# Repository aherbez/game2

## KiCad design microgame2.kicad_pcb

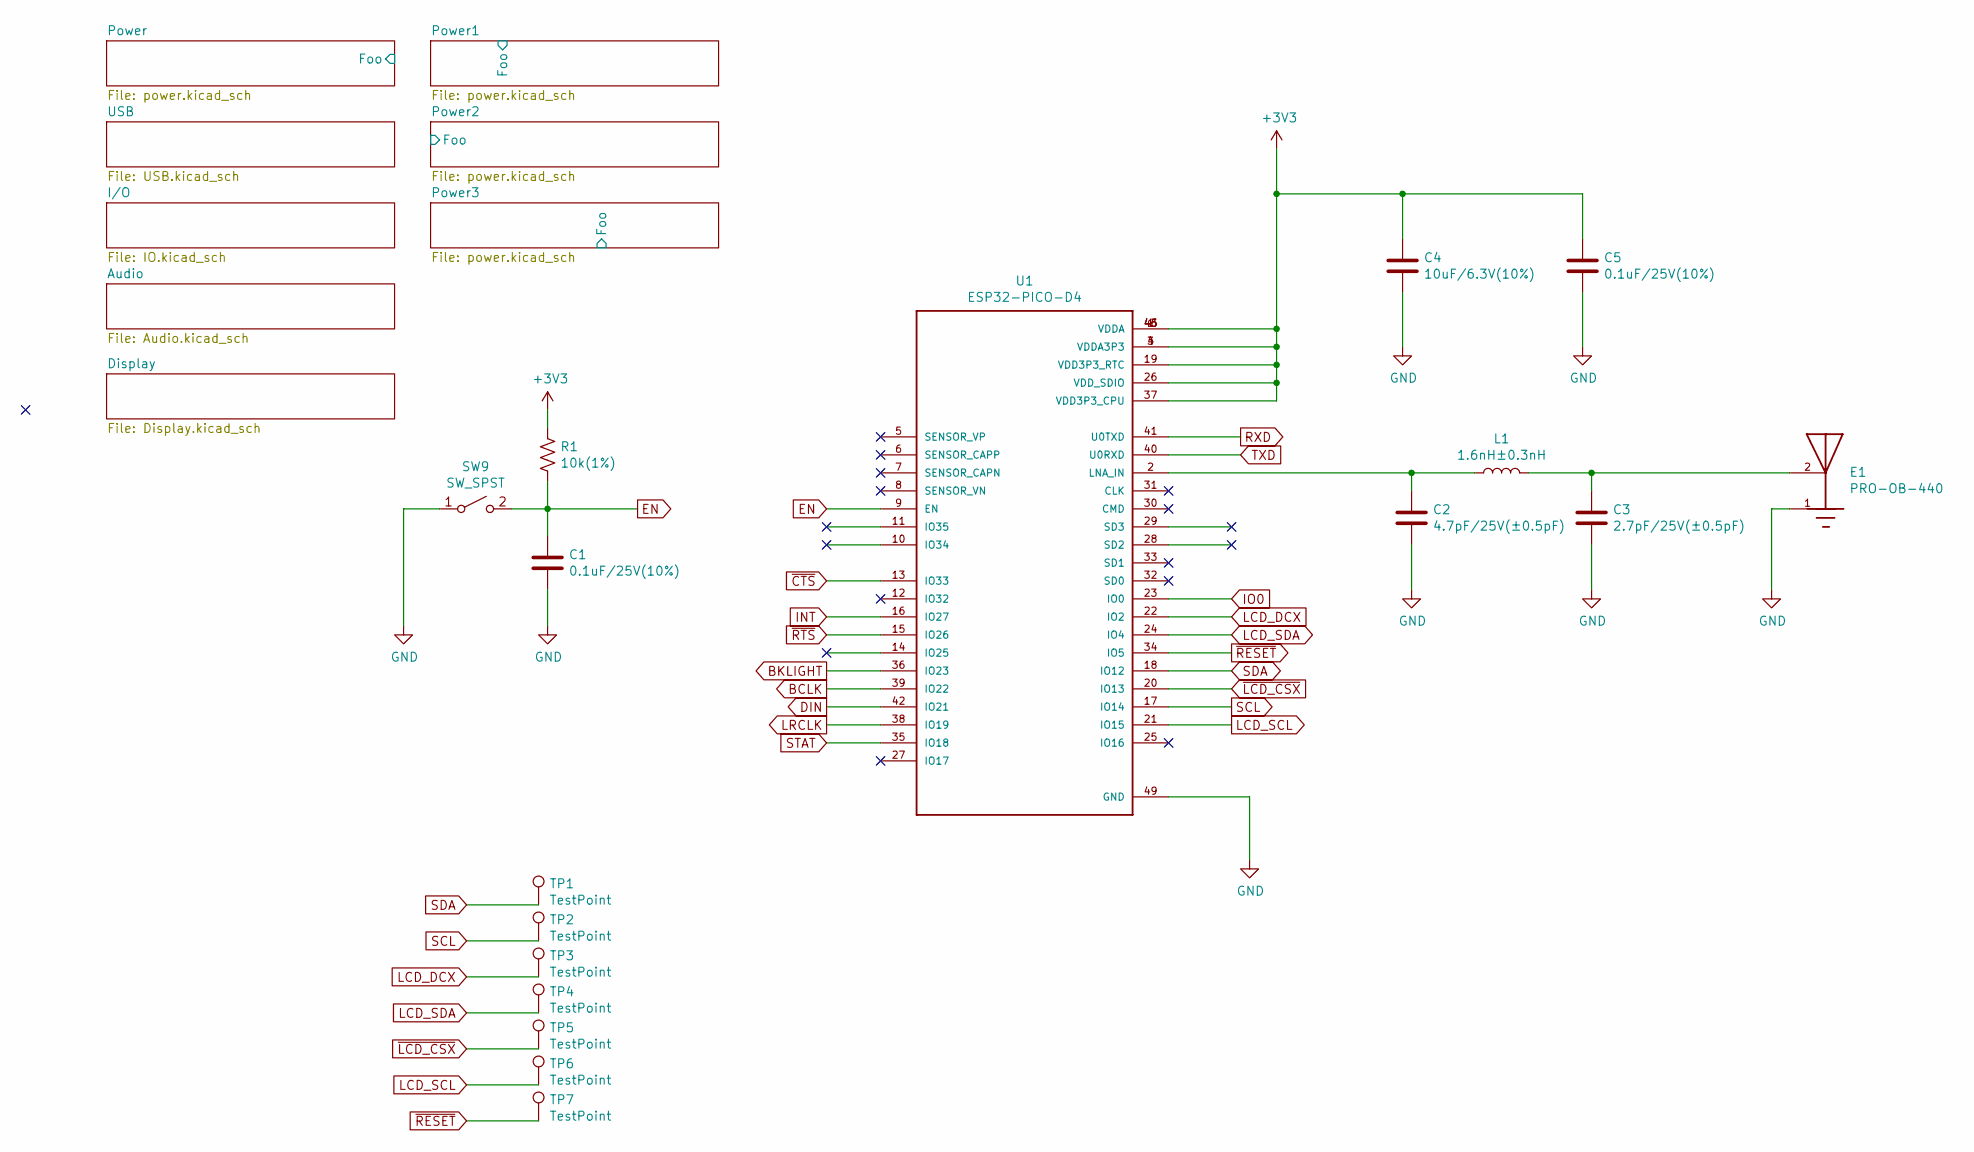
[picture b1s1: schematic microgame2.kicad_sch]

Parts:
C1, C5: 0.1uF/25V(10%); C_0402_1005Metric
C2: 4.7pF/25V(±0.5pF); C_0402_1005Metric
C3: 2.7pF/25V(±0.5pF); C_0402_1005Metric
C4: 10uF/6.3V(10%); C_0603_1608Metric
E1: PRO-OB-440; ANT_PRO-OB-440
L1: 1.6nH±0.3nH; C_0402_1005Metric
R1: 10k(1%); C_0402_1005Metric
SW9: SW_SPST; EVPAE
TP1, TP2, TP3, TP4, TP5, TP6, TP7: TestPoint; TestPoint_Pad_D1.0mm
U1: ESP32-PICO-D4; PQFN50P700X700X104-49N

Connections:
+3V3: C4.1, C5.1, R1.1, U1.1 (VDDA), U1.3 (VDDA3P3), U1.4 (VDDA3P3), U1.19 (VDD3P3_RTC), U1.26 (VDD_SDIO), U1.37 (VDD3P3_CPU), U1.43 (VDDA), U1.46 (VDDA); also elsewhere on the board
BCLK: U1.39 (IO22); also elsewhere on the board
BKLIGHT: U1.36 (IO23); also elsewhere on the board
DIN: U1.42 (IO21); also elsewhere on the board
EN: C1.1, R1.2, SW9.2 (B), U1.9 (EN); also elsewhere on the board
GND: C1.2, C2.2, C3.2, C4.2, C5.2, E1.1, SW9.1 (A), U1.49 (GND); also elsewhere on the board
INT: U1.16 (IO27); also elsewhere on the board
IO0: U1.23 (IO0); also elsewhere on the board
LCD_DCX: TP3.1, U1.22 (IO2); also elsewhere on the board
LCD_SCL: TP6.1, U1.21 (IO15); also elsewhere on the board
LCD_SDA: TP4.1, U1.24 (IO4); also elsewhere on the board
LRCLK: U1.38 (IO19); also elsewhere on the board
unnamed: C2.1, L1.1, U1.2 (LNA_IN)
unnamed: C3.1, E1.2, L1.2
RXD: U1.41 (U0TXD); also elsewhere on the board
SCL: TP2.1, U1.17 (IO14); also elsewhere on the board
SDA: TP1.1, U1.18 (IO12); also elsewhere on the board
STAT: U1.35 (IO18); also elsewhere on the board
TXD: U1.40 (U0RXD); also elsewhere on the board
~CTS: U1.13 (IO33); also elsewhere on the board
~LCD_CSX: TP5.1, U1.20 (IO13); also elsewhere on the board
~RESET: TP7.1, U1.34 (IO5); also elsewhere on the board
~RTS: U1.15 (IO26); also elsewhere on the board

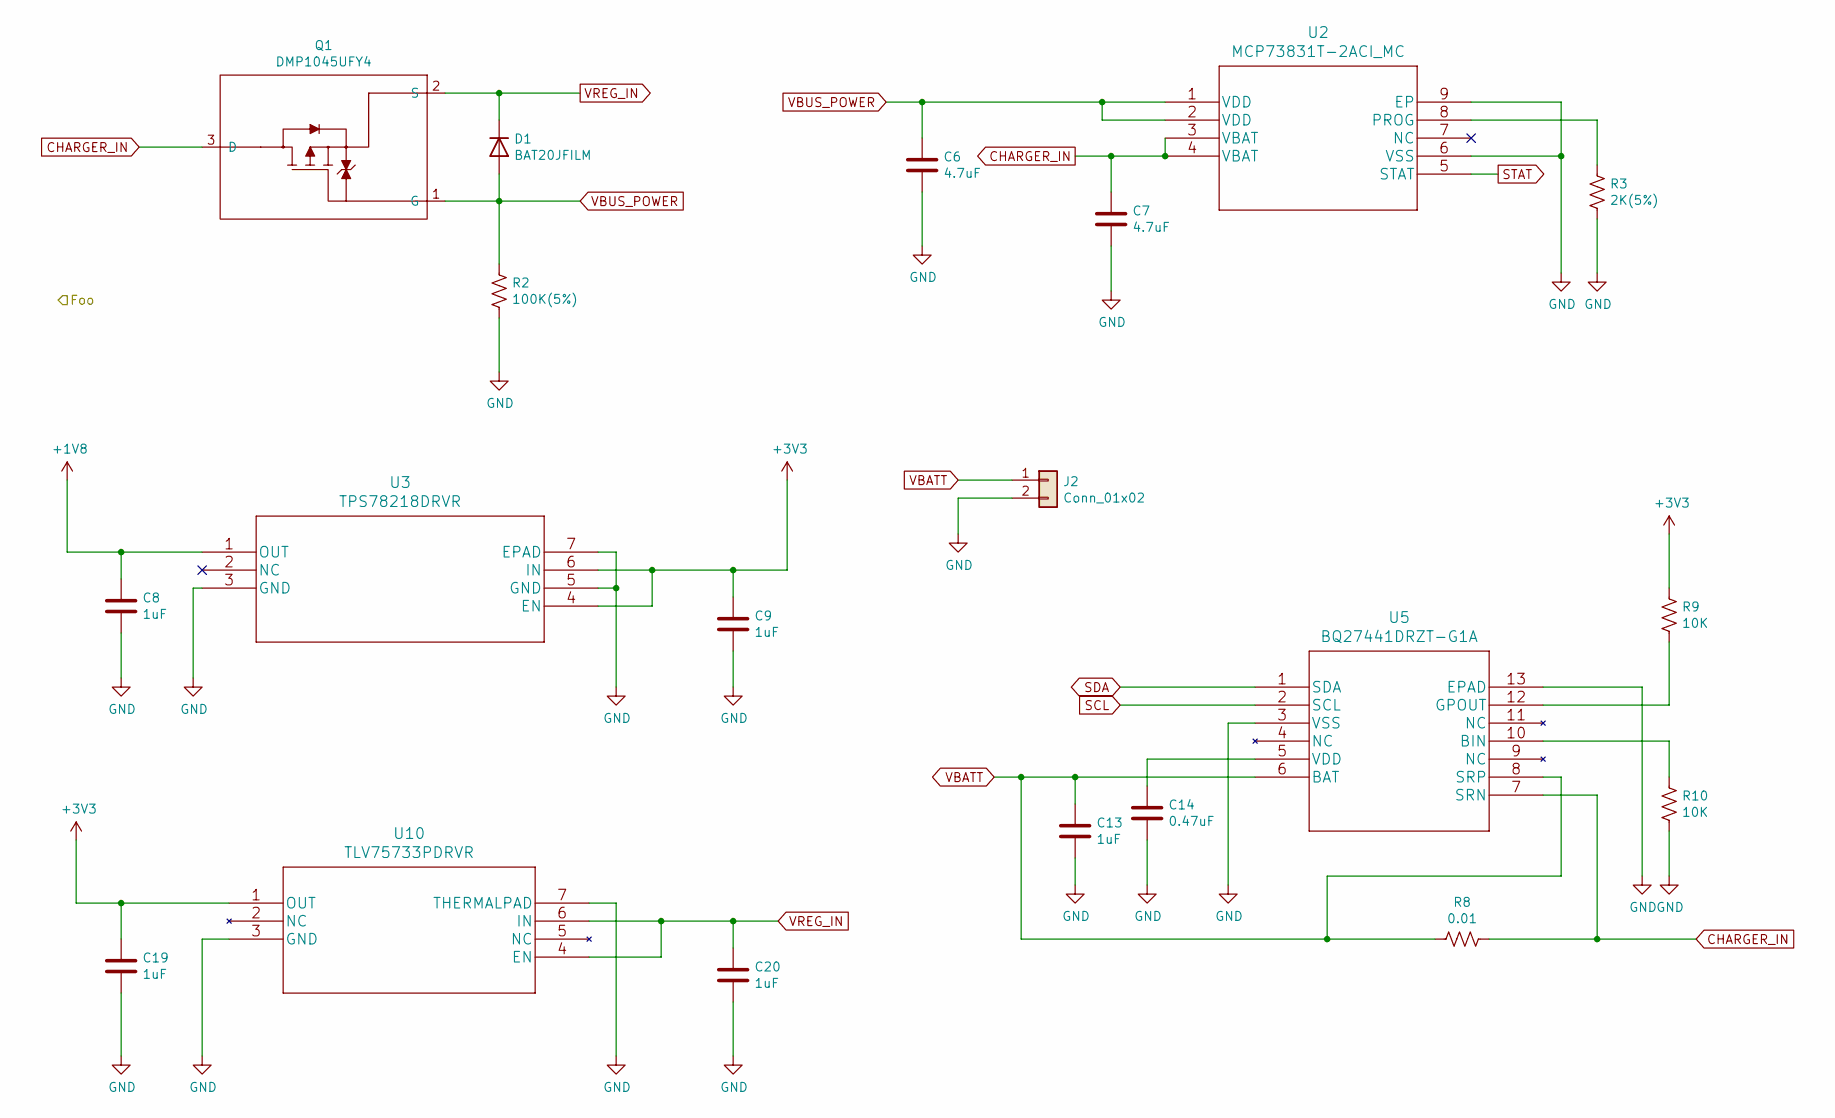
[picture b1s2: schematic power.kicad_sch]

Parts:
C6, C7: 4.7uF; R_0603_1608Metric
C8, C9, C13, C19, C20: 1uF; R_0603_1608Metric
C14: 0.47uF; R_0402_1005Metric
D1: ‎BAT20JFILM; BAT20JFILM
J2: Conn_01x02; R_1206_3216Metric
Q1: DMP1045UFY4; X2-DFN2015-3
R2: 100K(5%); R_0402_1005Metric
R3: 2K(5%); R_0402_1005Metric
R8: 0.01; R_1206_3216Metric
R9, R10: 10K; R_0402_1005Metric
U2: MCP73831T-2ACI_MC; MCP73831T-2ACI&slash_MC
U3: TPS78218DRVR
U5: BQ27441DRZT-G1A
U10: TLV75733PDRVR

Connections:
+1V8: C8.1, U3.1 (OUT); also elsewhere on the board
+3V3: C9.1, C19.1, R9.1, U3.4 (EN), U3.6 (IN), U10.1 (OUT); also elsewhere on the board
CHARGER_IN: C7.1, Q1.3 (D), R8.1, U2.3 (VBAT), U2.4 (VBAT), U5.7 (SRN)
GND: C6.2, C7.2, C8.2, C9.2, C13.2, C14.2, C19.2, C20.2, J2.2, R2.2, R3.2, R10.2, U2.6 (VSS), U2.9 (EP), U3.3 (GND), U3.5 (GND), U3.7 (EPAD), U5.3 (VSS), U5.13 (EPAD), U10.3 (GND), U10.7 (THERMALPAD); also elsewhere on the board
unnamed: C14.1, U5.5 (VDD)
unnamed: R3.1, U2.8 (PROG)
unnamed: R9.2, U5.12 (GPOUT)
unnamed: R10.1, U5.10 (BIN)
SCL: U5.2 (SCL); also elsewhere on the board
SDA: U5.1 (SDA); also elsewhere on the board
STAT: U2.5 (STAT); also elsewhere on the board
VBATT: C13.1, J2.1, R8.2, U5.6 (BAT), U5.8 (SRP)
VBUS_POWER: C6.1, D1.2 (A), Q1.1 (G), R2.1, U2.1 (VDD), U2.2 (VDD); also elsewhere on the board
VREG_IN: C20.1, D1.1 (K), Q1.2 (S), U10.4 (EN), U10.6 (IN)

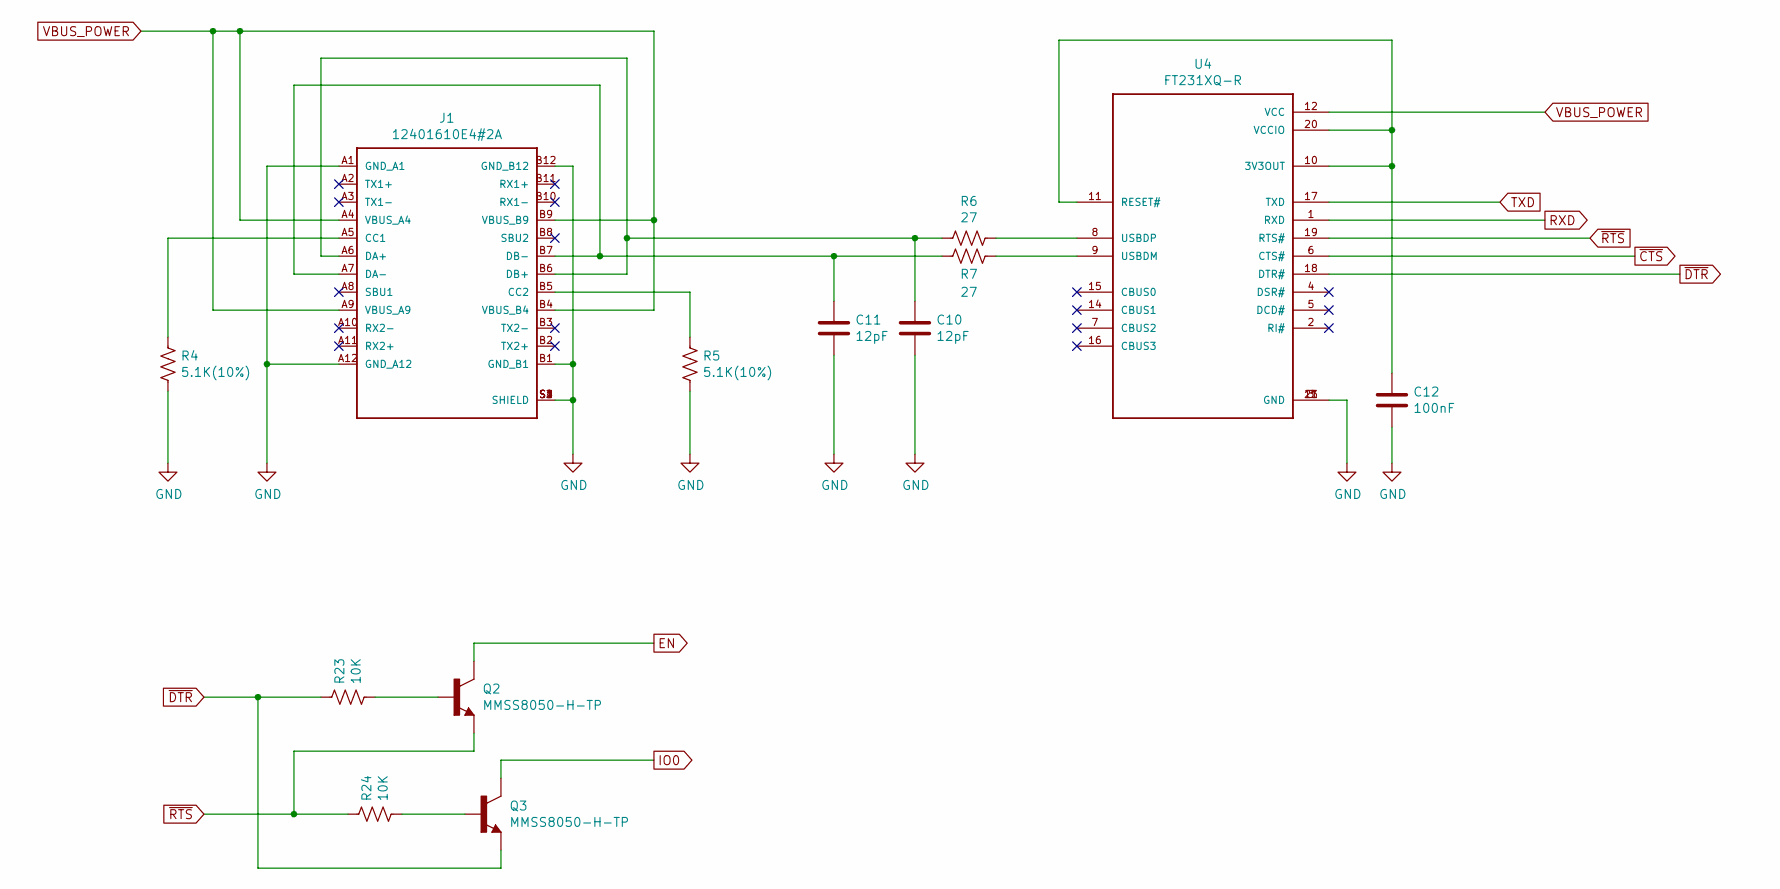
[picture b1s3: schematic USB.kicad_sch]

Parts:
C10, C11: 12pF; R_0402_1005Metric
C12: 100nF; R_0402_1005Metric
J1: 12401610E4#2A; AMPHENOL_12401610E4#2A
Q2, Q3: MMSS8050-H-TP; TRANS_MMSS8050-H-TP
R4, R5: 5.1K(10%); R_0402_1005Metric
R6, R7: 27; R_0402_1005Metric
R23, R24: 10K; R_0402_1005Metric
U4: FT231XQ-R; QFN50P400X400X80-21N

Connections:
EN: Q2.3; also elsewhere on the board
GND: C10.2, C11.2, C12.2, J1.A1 (GND_A1), J1.A12 (GND_A12), J1.B1 (GND_B1), J1.B12 (GND_B12), J1.S1 (SHIELD), J1.S2 (SHIELD), J1.S3 (SHIELD), J1.S4 (SHIELD), R4.1, R5.1, U4.3 (GND), U4.13 (GND), U4.21 (GND); also elsewhere on the board
IO0: Q3.3; also elsewhere on the board
unnamed: C10.1, J1.A6 (DA+), J1.B6 (DB+), R6.2
unnamed: C11.1, J1.A7 (DA-), J1.B7 (DB-), R7.2
unnamed: C12.1, U4.10 (3V3OUT), U4.11 (RESET#), U4.20 (VCCIO)
unnamed: J1.A5 (CC1), R4.2
unnamed: J1.B5 (CC2), R5.2
unnamed: Q2.1, R23.1
unnamed: Q3.1, R24.1
unnamed: R6.1, U4.8 (USBDP)
unnamed: R7.1, U4.9 (USBDM)
RXD: U4.1 (RXD); also elsewhere on the board
TXD: U4.17 (TXD); also elsewhere on the board
VBUS_POWER: J1.A4 (VBUS_A4), J1.A9 (VBUS_A9), J1.B4 (VBUS_B4), J1.B9 (VBUS_B9), U4.12 (VCC); also elsewhere on the board
~CTS: U4.6 (CTS#); also elsewhere on the board
~DTR: Q3.2, R23.2, U4.18 (DTR#)
~RTS: Q2.2, R24.2, U4.19 (RTS#); also elsewhere on the board

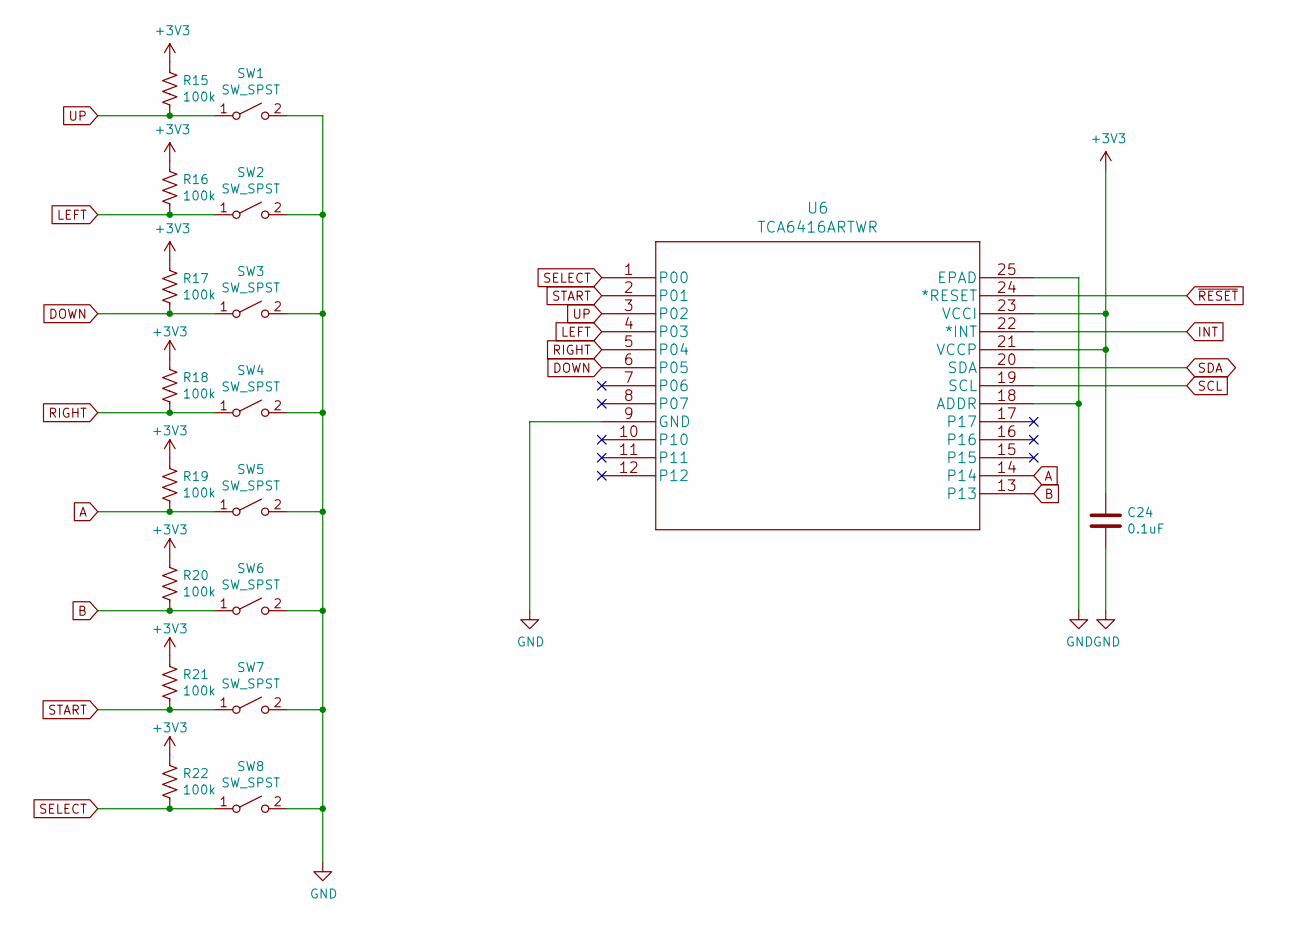
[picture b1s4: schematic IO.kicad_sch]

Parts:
C24: 0.1uF; C_0402_1005Metric
R15, R16, R17, R18, R19, R20, R21, R22: 100k; R_0402_1005Metric
SW1, SW2, SW3, SW4, SW5, SW6, SW7, SW8: SW_SPST; Button_Pad
U6: TCA6416ARTWR

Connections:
+3V3: C24.1, R15.1, R16.1, R17.1, R18.1, R19.1, R20.1, R21.1, R22.1, U6.21 (VCCP), U6.23 (VCCI); also elsewhere on the board
A: R19.2, SW5.1 (A), U6.14
B: R20.2, SW6.1 (A), U6.13
DOWN: R17.2, SW3.1 (A), U6.6 (P05)
GND: C24.2, SW1.2 (B), SW2.2 (B), SW3.2 (B), SW4.2 (B), SW5.2 (B), SW6.2 (B), SW7.2 (B), SW8.2 (B), U6.9 (GND), U6.18 (ADDR), U6.25 (EPAD); also elsewhere on the board
INT: U6.22 (*INT); also elsewhere on the board
LEFT: R16.2, SW2.1 (A), U6.4 (P03)
RIGHT: R18.2, SW4.1 (A), U6.5 (P04)
SCL: U6.19 (SCL); also elsewhere on the board
SDA: U6.20 (SDA); also elsewhere on the board
SELECT: R22.2, SW8.1 (A), U6.1 (P00)
START: R21.2, SW7.1 (A), U6.2 (P01)
UP: R15.2, SW1.1 (A), U6.3 (P02)
~RESET: U6.24 (*RESET); also elsewhere on the board

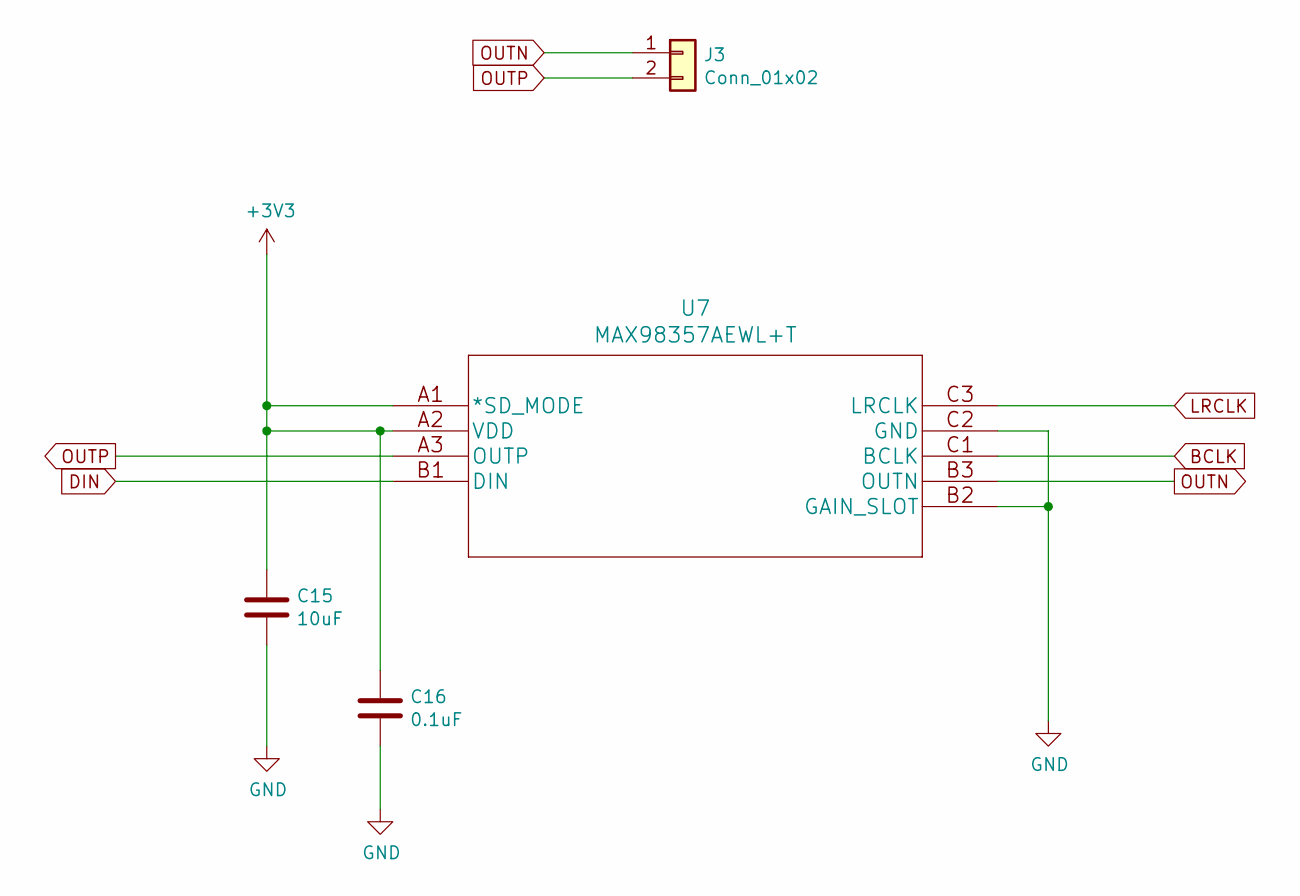
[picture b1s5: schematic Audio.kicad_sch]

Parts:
C15: 10uF; R_0603_1608Metric
C16: 0.1uF; R_0402_1005Metric
J3: Conn_01x02; R_1206_3216Metric
U7: MAX98357AEWL+T; MAX98357AEWL&plus_T

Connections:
+3V3: C15.1, C16.1, U7.A1 (*SD_MODE), U7.A2 (VDD); also elsewhere on the board
BCLK: U7.C1 (BCLK); also elsewhere on the board
DIN: U7.B1 (DIN); also elsewhere on the board
GND: C15.2, C16.2, U7.B2 (GAIN_SLOT), U7.C2 (GND); also elsewhere on the board
LRCLK: U7.C3 (LRCLK); also elsewhere on the board
OUTN: J3.1, U7.B3 (OUTN)
OUTP: J3.2, U7.A3 (OUTP)

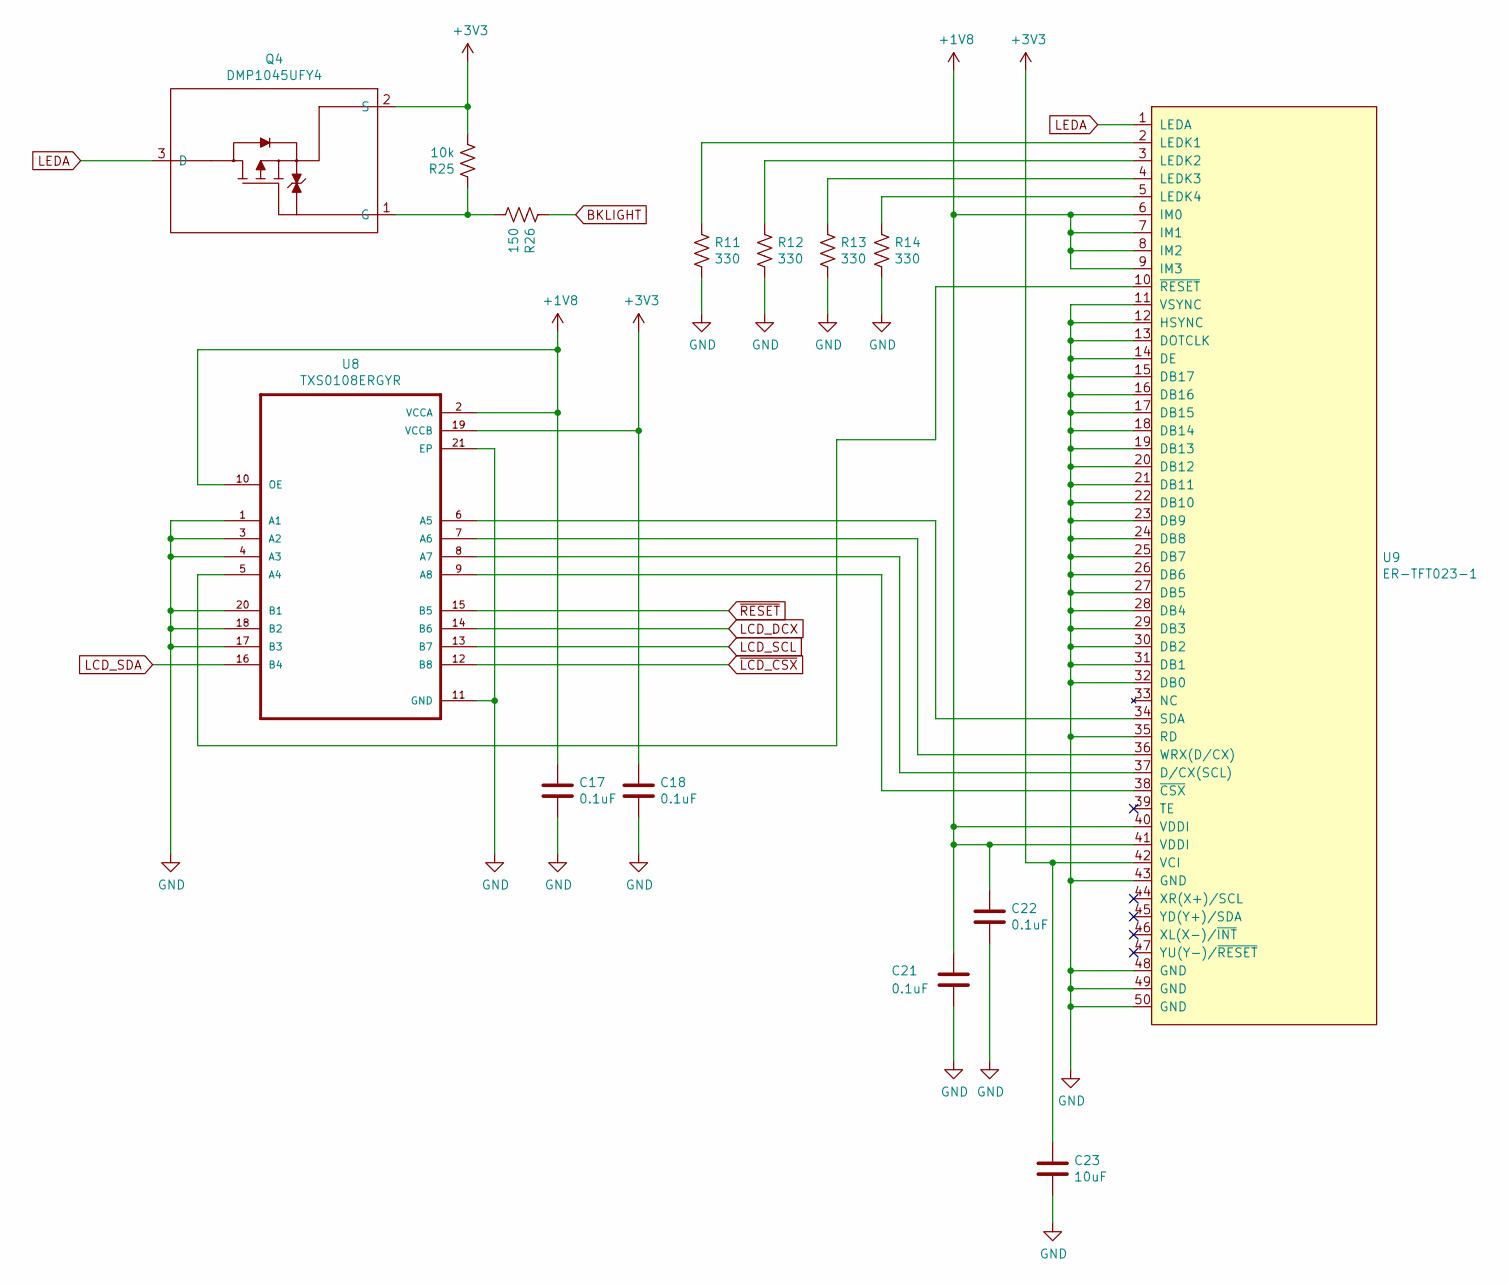
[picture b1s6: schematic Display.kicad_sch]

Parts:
C17, C18, C21, C22: 0.1uF; R_0402_1005Metric
C23: 10uF; C_0603_1608Metric
Q4: DMP1045UFY4; X2-DFN2015-3
R11, R12, R13, R14: 330; R_0402_1005Metric
R25: 10k; R_0402_1005Metric
R26: 150; R_0402_1005Metric
U8: TXS0108ERGYR; QFN50P450X350X100-21N
U9: ER-TFT023-1; ER-CON50HT-1-INV

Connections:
+1V8: C17.1, C21.1, C22.1, U8.2 (VCCA), U8.10 (OE), U9.6 (IM0), U9.7 (IM1), U9.8 (IM2), U9.9 (IM3), U9.40 (VDDI), U9.41 (VDDI); also elsewhere on the board
+3V3: C18.1, C23.1, Q4.2 (S), R25.2, U8.19 (VCCB), U9.42 (VCI); also elsewhere on the board
BKLIGHT: R26.1; also elsewhere on the board
GND: C17.2, C18.2, C21.2, C22.2, C23.2, R11.2, R12.2, R13.2, R14.2, U8.1 (A1), U8.3 (A2), U8.4 (A3), U8.11 (GND), U8.17 (B3), U8.18 (B2), U8.20 (B1), U8.21 (EP), U9.11 (VSYNC), U9.12 (HSYNC), U9.13 (DOTCLK), U9.14 (DE), U9.15 (DB17), U9.16 (DB16), U9.17 (DB15), U9.18 (DB14), U9.19 (DB13), U9.20 (DB12), U9.21 (DB11), U9.22 (DB10), U9.23 (DB9), U9.24 (DB8), U9.25 (DB7), U9.26 (DB6), U9.27 (DB5), U9.28 (DB4), U9.29 (DB3), U9.30 (DB2), U9.31 (DB1), U9.32 (DB0), U9.35 (RD), U9.43 (GND), U9.48 (GND), U9.49 (GND), U9.50 (GND); also elsewhere on the board
LCD_DCX: U8.14 (B6); also elsewhere on the board
LCD_SCL: U8.13 (B7); also elsewhere on the board
LCD_SDA: U8.16 (B4); also elsewhere on the board
LEDA: Q4.3 (D), U9.1 (LEDA)
unnamed: Q4.1 (G), R25.1, R26.2
unnamed: R11.1, U9.2 (LEDK1)
unnamed: R12.1, U9.3 (LEDK2)
unnamed: R13.1, U9.4 (LEDK3)
unnamed: R14.1, U9.5 (LEDK4)
unnamed: U8.5 (A4), U9.10 (~RESET)
unnamed: U8.6 (A5), U9.34 (SDA)
unnamed: U8.7 (A6), U9.36 (WRX(D/CX))
unnamed: U8.8 (A7), U9.37 (D/CX(SCL))
unnamed: U8.9 (A8), U9.38 (~CSX)
~LCD_CSX: U8.12 (B8); also elsewhere on the board
~RESET: U8.15 (B5); also elsewhere on the board

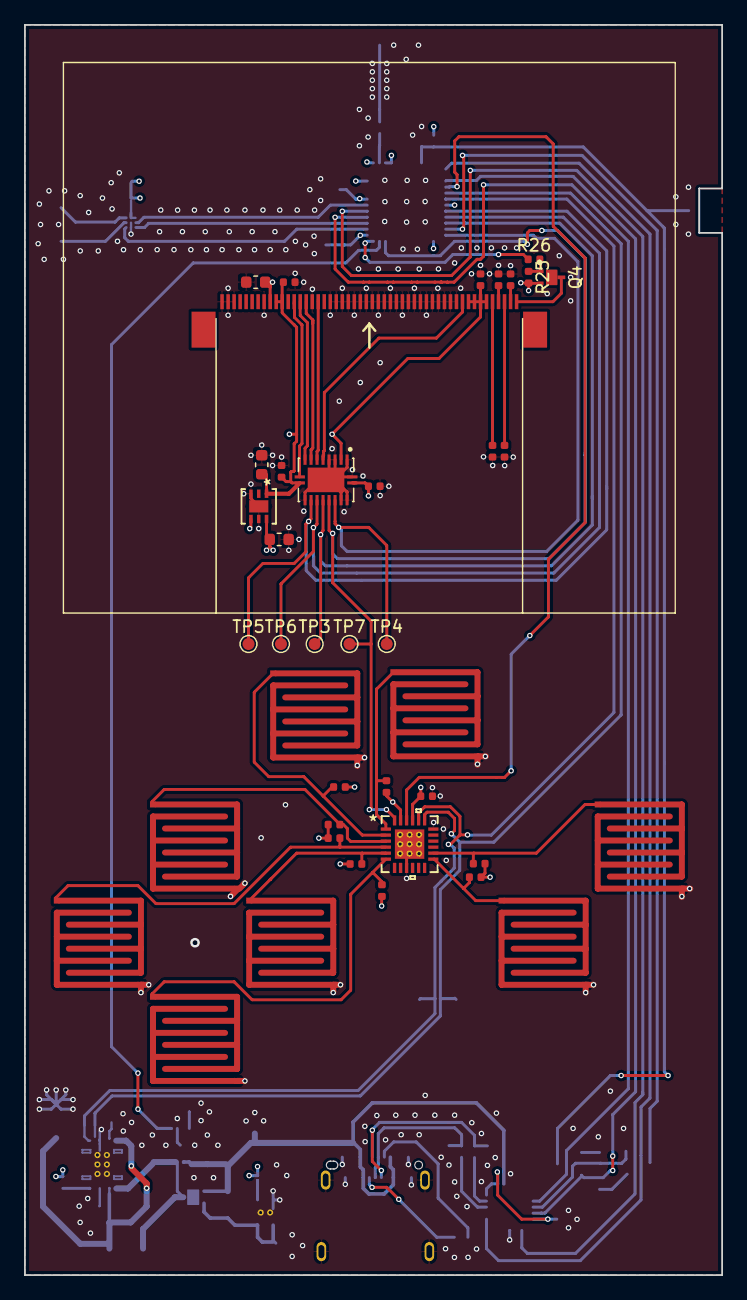
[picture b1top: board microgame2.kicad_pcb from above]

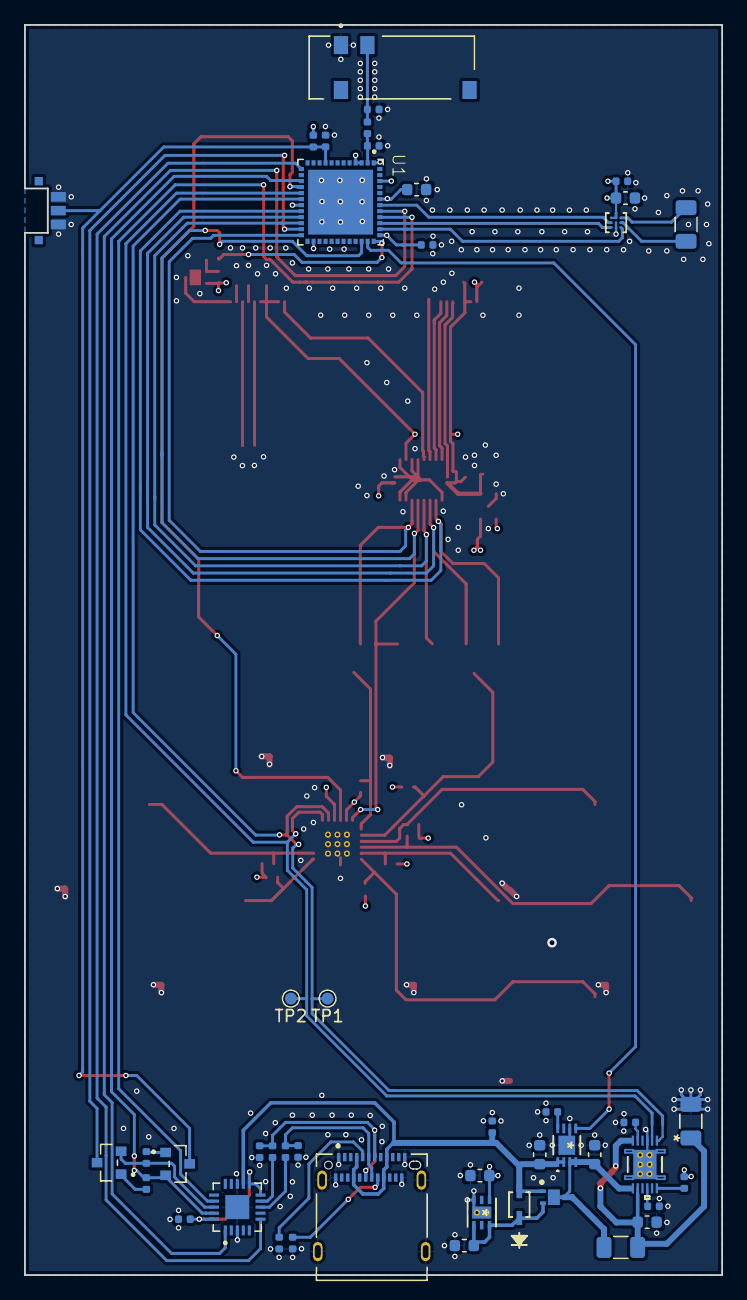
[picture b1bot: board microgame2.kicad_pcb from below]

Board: 4 copper layers, 58.0 x 104.0 mm, 86 parts (46 on the bottom side), 63 nets.

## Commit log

2024-06-25 initial checkin
2024-06-25 reverting pin movement

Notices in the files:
parts and their libraries:
Copyright 2016 Accelerated Designs. All rights reserved.
